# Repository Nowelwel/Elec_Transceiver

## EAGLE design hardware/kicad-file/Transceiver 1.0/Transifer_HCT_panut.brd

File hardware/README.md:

# Dokumentasi Transceiver
Folder ini berisi semua file hardware untuk proyek **Transceiver Board**. Gunakan Software di bawah ini untuk akses file Hardware
- [KiCad](https://kicad.org/)
- [Eagle](https://www.autodesk.com/products/eagle) 

## 📃 Schematic
Berikut adalah schematic dari Transceiver Board 2.0. 

## BOM
Berikut adalah BOM board Transceiver 2.0.

|References|Quantity|Package|Value|Desc|
|:-:|:------:|:----:|:---:|:--:|
|C1|1|0805|100nF|Capacitor|
|R13, R16-R18, R21-R24|8|0805|330R|Resistor|
|R19, R20, R30, R31|4|0805|10K|Resistor|
|LED1, LED 2|2|1206| - | LED|
|IC1|1|SO14|74HCT14D|Hex inverter with Schmitt-trigger inputs|
|IC2|1|SO14|74HCT125D|Quad buffer|
|D1|1|SOT-23|SRV05-4|Diode array|
|U$1|1|TRANSCEIVER_2.0|TRANSCEIVER_2.0|Socket|

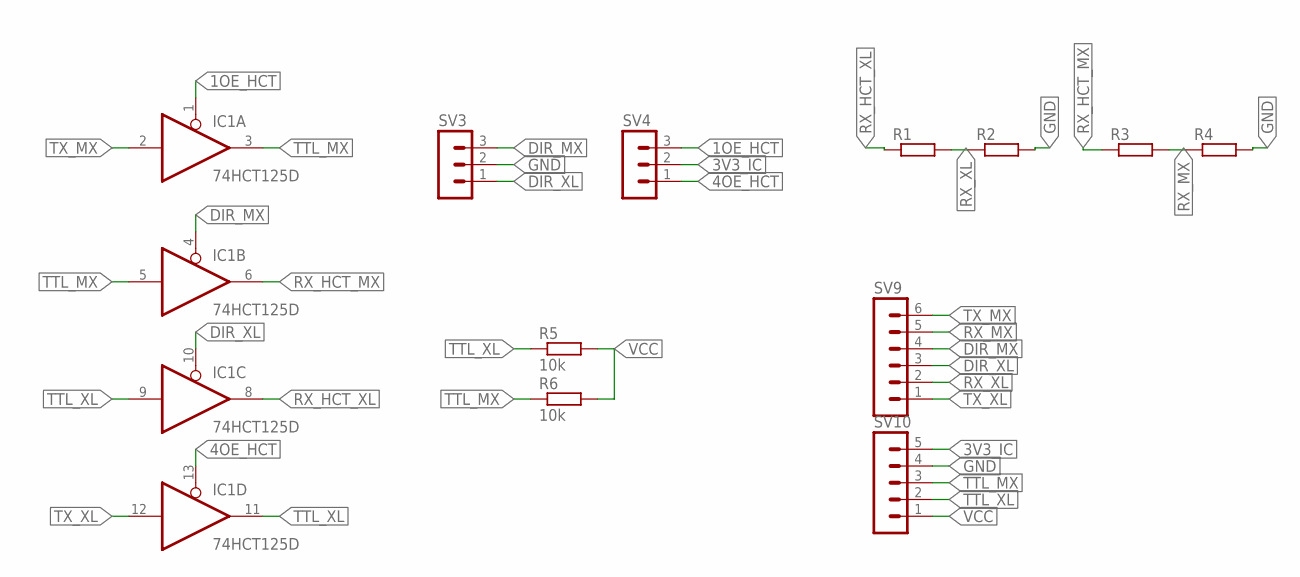
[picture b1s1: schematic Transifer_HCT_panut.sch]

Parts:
IC1: 74HCT125D; SO14
R1, R2, R3, R4: R-EU_R1206; R1206
R5, R6: 10k; R1206
SV3, SV4: MA03-1
SV9: MA06-1
SV10: MA05-1

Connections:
1OE_HCT: IC1.1 (OE), SV4.3
3V3_IC: SV4.2, SV10.5
4OE_HCT: IC1.13 (OE), SV4.1
DIR_MX: IC1.4 (OE), SV3.3, SV9.4
DIR_XL: IC1.10 (OE), SV3.1, SV9.3
GND: IC1.7 (GND), R2.2, R4.2, SV3.2, SV10.4
RX_HCT_MX: IC1.6 (O), R3.1
RX_HCT_XL: IC1.8 (O), R1.1
RX_MX: R3.2, R4.1, SV9.5
RX_XL: R1.2, R2.1, SV9.2
TTL_MX: IC1.3 (O), IC1.5 (I), R6.1, SV10.3
TTL_XL: IC1.9 (I), IC1.11 (O), R5.1, SV10.2
TX_MX: IC1.2 (I), SV9.6
TX_XL: IC1.12 (I), SV9.1
VCC: IC1.14 (VCC), R5.2, R6.2, SV10.1

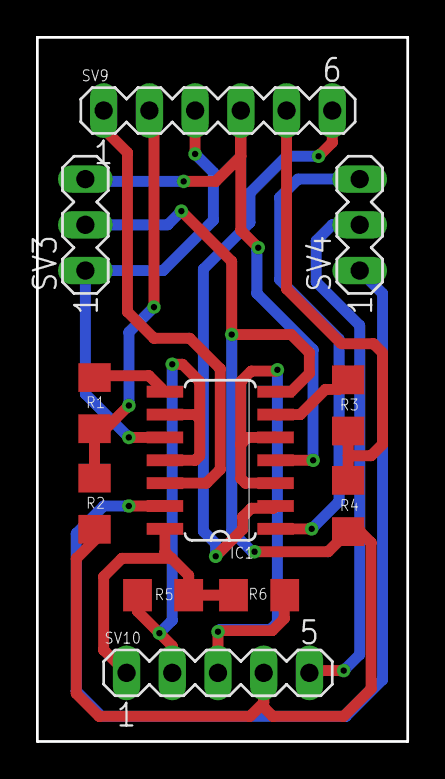
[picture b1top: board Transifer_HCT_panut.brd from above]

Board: 2 copper layers, 20.6 x 39.1 mm, 11 parts (0 on the bottom side), 15 nets.

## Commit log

2025-07-26 add .gitkeep
2025-07-26 add design-files
2025-07-26 add exports
2025-07-26 add README for hardware
2025-07-26 add.gitkeep
2025-07-26 add Transceiver 2.0 image
2025-07-26 schematic 2.0
2025-07-26 Rename Transceiver 2.0 Schematic.jpg to schematic.jpg
2025-07-26 Rename Transceiver 1.0 to p
2025-07-26 Create p
2025-07-26 add Transceiver 1.0 sch
2025-07-26 Rename Transifer_HCT_panut.sch to Transceiver 1.0 sch
2025-07-26 add Transceiver 1.0 brd
2025-07-26 Rename Transifer_HCT_panut.brd to Transceiver 1.0 brd.brd
2025-07-26 Rename Transceiver 1.0 brd.brd to Transceiver 1.0 board.brd
2025-07-26 add transceiver 1.o sch
2025-07-26 Rename Transifer_HCT_panut.sch to Transceiver 1.0 .sch
2025-07-26 Rename Transceiver 1.0 .sch to Transceiver 1.0.sch
2025-07-26 Rename Transceiver 1.0 board.brd to Transceiver 1.0.brd
2025-07-26 add transceiver 2.0 pro
2025-07-26 add transceiver 2.0 sch
2025-07-26 add transceiver 2.0 brd
2025-07-26 Rename transceiver 2.0.kicad_pro to Transceiver 2.0.kicad_pro
2025-07-26 add transceiver 3.0 files
2025-07-26 add transceiver 3.0 board
2025-07-26 Rename transciverSMD.kicad_pro to Transceiver 3.0.kicad_pro
2025-07-27 add CHANGELOG.md
2025-07-27 add transceiver 2.0 html
2025-07-27 add transceiver 2.0 bom image
